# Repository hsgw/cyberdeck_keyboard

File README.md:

# 10x3 Keyboard pcb for Cyberdeck

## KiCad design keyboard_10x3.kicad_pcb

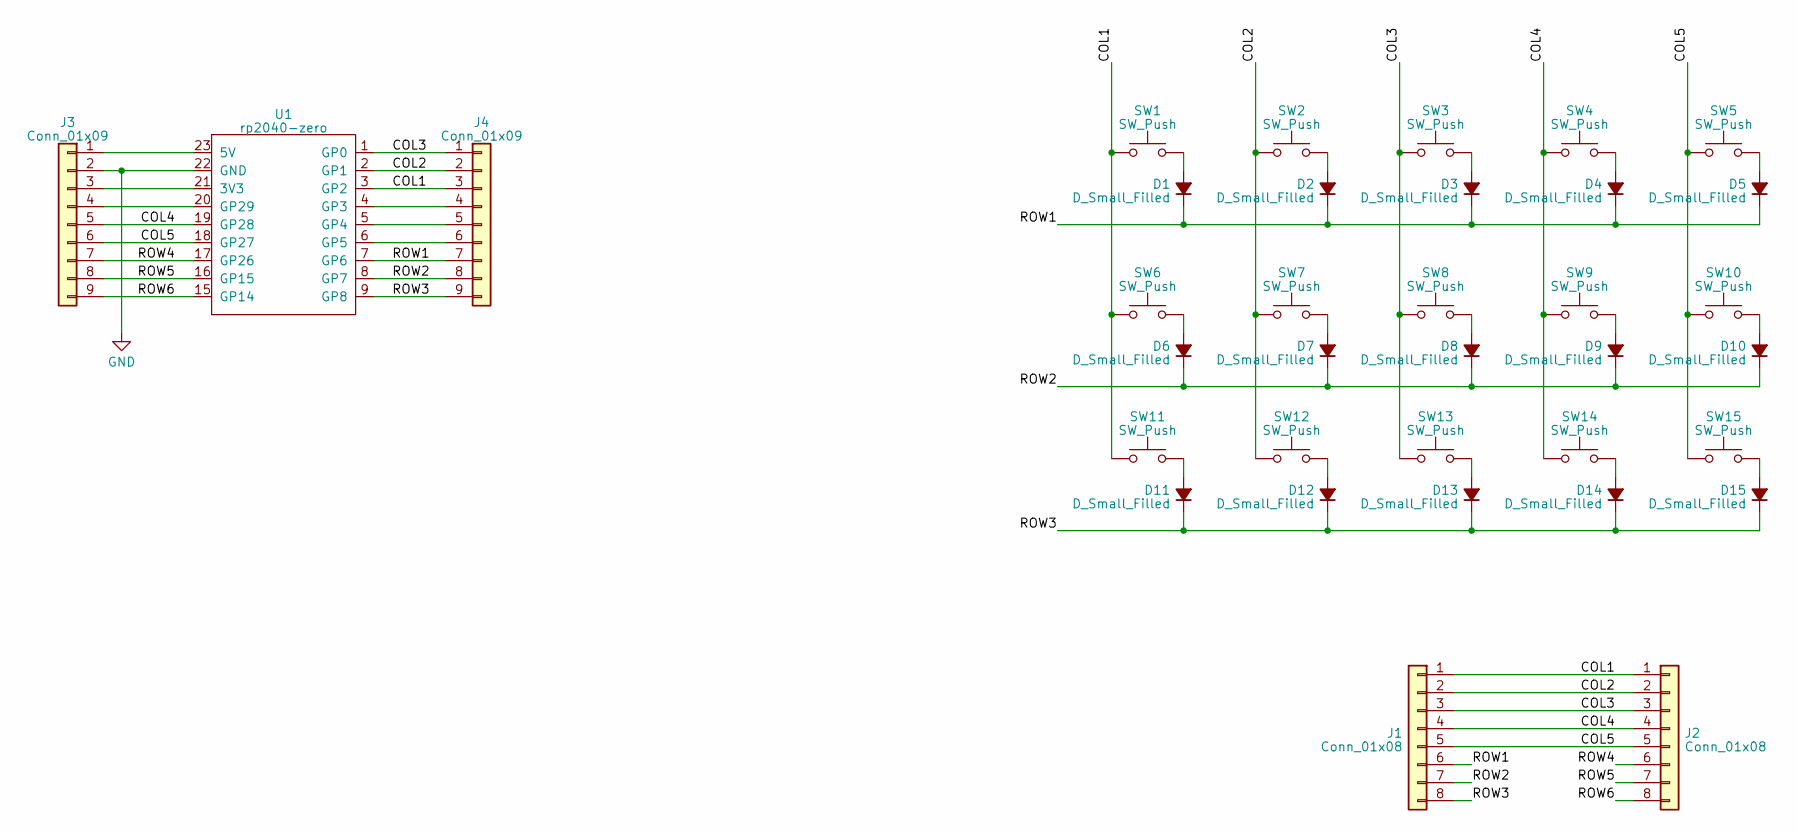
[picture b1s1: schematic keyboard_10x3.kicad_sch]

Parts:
D1, D2, D3, D4, D5, D6, D7, D8, D9, D10, D11, D12, D13, D14, D15: D_Small_Filled; D_SOD123_hand
J1, J2: Conn_01x08; PinHeader_1x08_P2.54mm_Vertical
J3, J4: Conn_01x09; PinHeader_1x09_P2.54mm_Vertical
SW1, SW2, SW3, SW4, SW5, SW6, SW7, SW8, SW9, SW10, SW11, SW12, SW13, SW14, SW15: SW_Push; SW_Cherry_MX1A_1.00u_PCB
U1: rp2040-zero; rp2040-zero-side-th

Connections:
/COL1: J1.1, J2.1, J4.3, SW1.2, SW6.2, SW11.2, U1.3 (GP2)
/COL2: J1.2, J2.2, J4.2, SW2.2, SW7.2, SW12.2, U1.2 (GP1)
/COL3: J1.3, J2.3, J4.1, SW3.2, SW8.2, SW13.2, U1.1 (GP0)
/COL4: J1.4, J2.4, J3.5, SW4.2, SW9.2, SW14.2, U1.19 (GP28)
/COL5: J1.5, J2.5, J3.6, SW5.2, SW10.2, SW15.2, U1.18 (GP27)
/ROW1: D1.1 (K), D2.1 (K), D3.1 (K), D4.1 (K), D5.1 (K), J1.6, J4.7, U1.7 (GP6)
/ROW2: D6.1 (K), D7.1 (K), D8.1 (K), D9.1 (K), D10.1 (K), J1.7, J4.8, U1.8 (GP7)
/ROW3: D11.1 (K), D12.1 (K), D13.1 (K), D14.1 (K), D15.1 (K), J1.8, J4.9, U1.9 (GP8)
/ROW4: J2.6, J3.7, U1.17 (GP26)
/ROW5: J2.7, J3.8, U1.16 (GP15)
/ROW6: J2.8, J3.9, U1.15 (GP14)
GND: J3.2, U1.22 (GND)
unnamed: D1.2 (A), SW1.1
unnamed: D2.2 (A), SW2.1
unnamed: D3.2 (A), SW3.1
unnamed: D4.2 (A), SW4.1
unnamed: D5.2 (A), SW5.1
unnamed: D6.2 (A), SW6.1
unnamed: D7.2 (A), SW7.1
unnamed: D8.2 (A), SW8.1
unnamed: D9.2 (A), SW9.1
unnamed: D10.2 (A), SW10.1
unnamed: D11.2 (A), SW11.1
unnamed: D12.2 (A), SW12.1
unnamed: D13.2 (A), SW13.1
unnamed: D14.2 (A), SW14.1
unnamed: D15.2 (A), SW15.1
unnamed: J3.1, U1.23 (5V)
unnamed: J3.3, U1.21 (3V3)
unnamed: J3.4, U1.20 (GP29)
unnamed: J4.4, U1.4 (GP3)
unnamed: J4.5, U1.5 (GP4)
unnamed: J4.6, U1.6 (GP5)

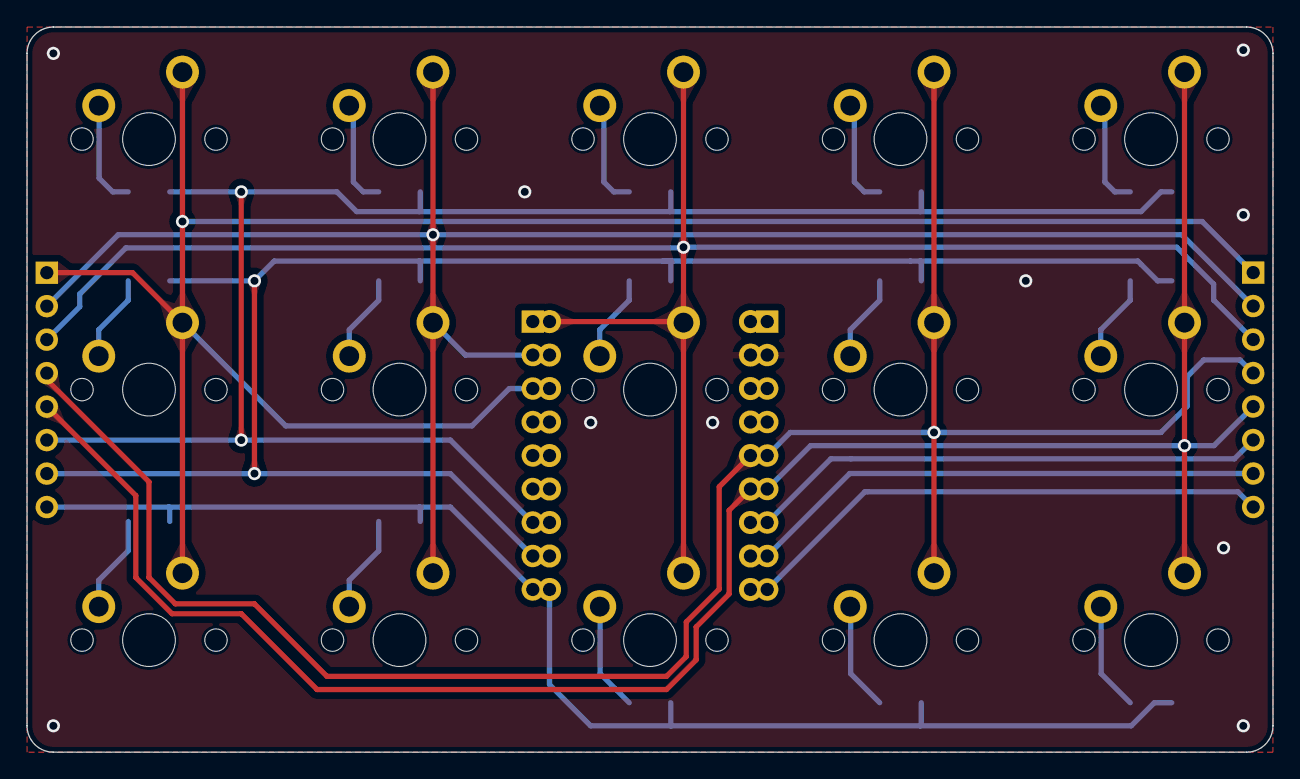
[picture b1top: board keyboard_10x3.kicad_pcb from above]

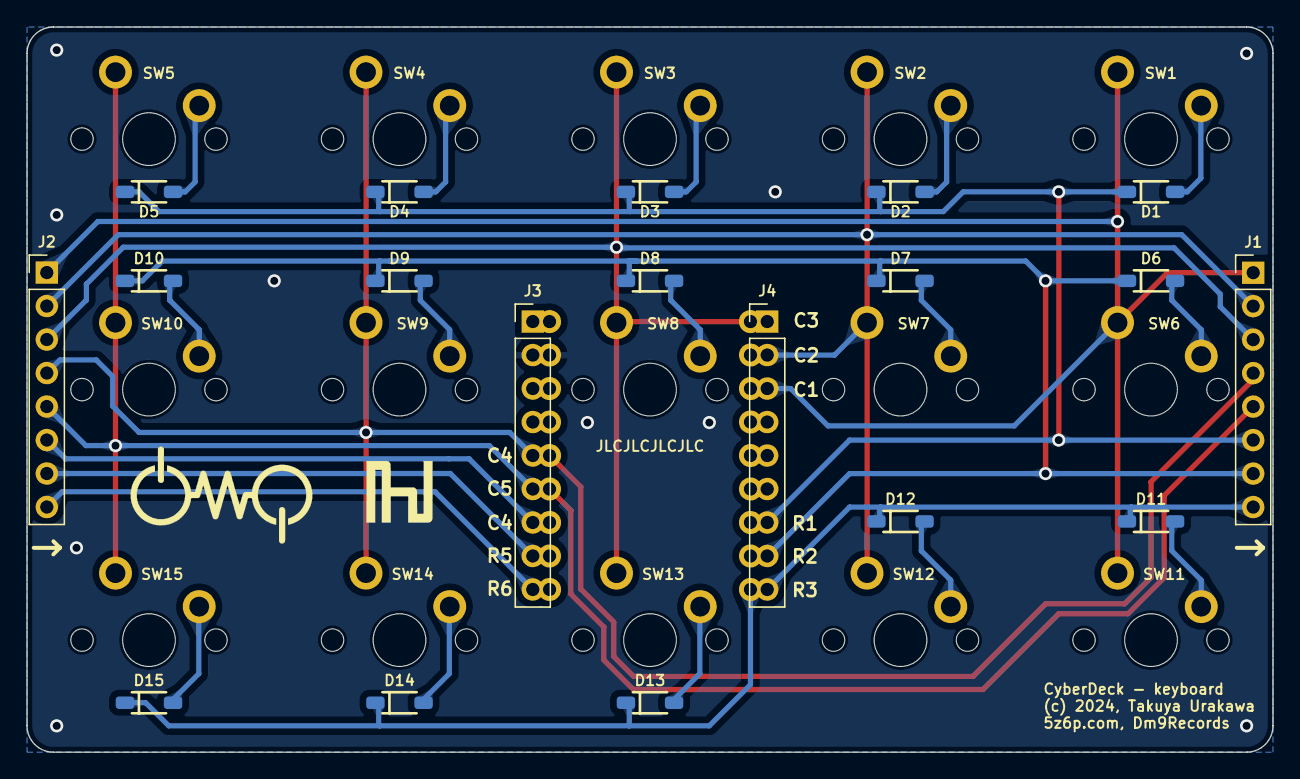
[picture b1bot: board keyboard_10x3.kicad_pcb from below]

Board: 2 copper layers, 94.5 x 55.0 mm, 35 parts (20 on the bottom side), 33 nets.

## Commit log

2025-02-21 Create LICENSE

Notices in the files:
keyboard_10x3.kicad_pcb:
(c) 2024, Takuya Urakawa
